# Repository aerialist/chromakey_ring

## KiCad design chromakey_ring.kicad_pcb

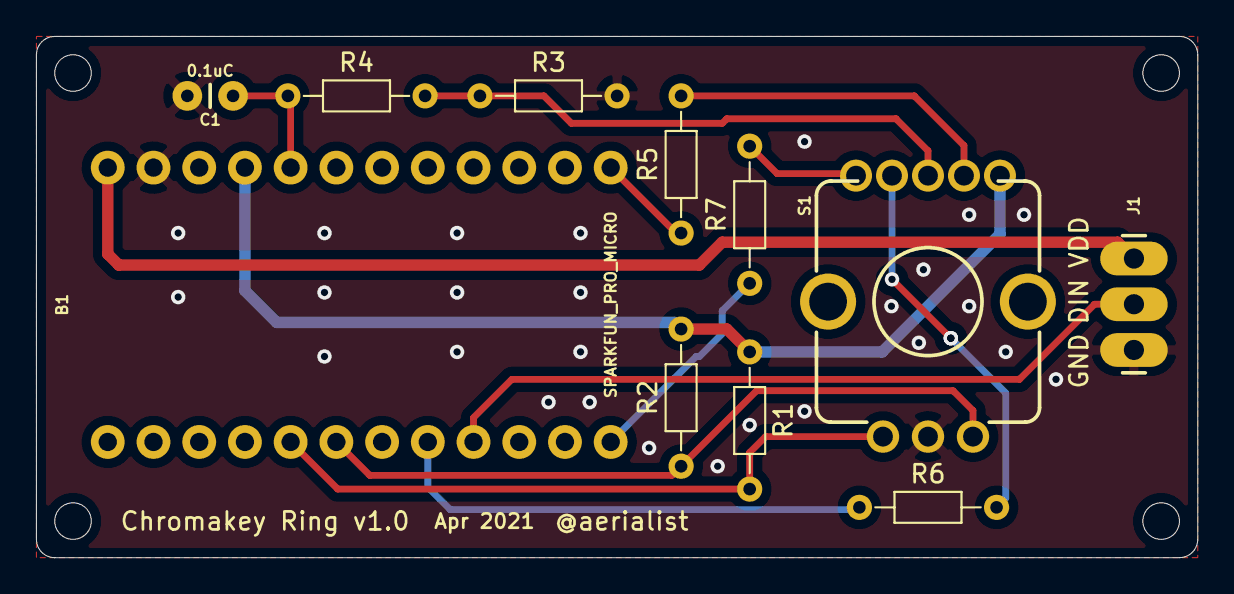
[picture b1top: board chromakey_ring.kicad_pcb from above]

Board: 2 copper layers, 64.5 x 29.0 mm, 11 parts (0 on the bottom side), 14 nets.

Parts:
B1: SPARKFUN_PRO_MICRO
C1: 0.1uC; CAP-PTH-2.54
J1: Conn_01x03; 1X03_LONGPADS
R1, R2, R3: 10kR; R_Axial_DIN0204_L3.6mm_D1.6mm_P7.62mm_Horizontal
R4: 1kR; R_Axial_DIN0204_L3.6mm_D1.6mm_P7.62mm_Horizontal
R5, R6, R7: 330R; R_Axial_DIN0204_L3.6mm_D1.6mm_P7.62mm_Horizontal
S1: ENCODER-RGB-SWITCH; ENCODER_LED_3

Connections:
+5V: B1.21, R1.1, R2.2, S1.5
/A: B1.5, R1.2, S1.A
/B: B1.6, R2.1, S1.B
/DIN: B1.9, J1.2
/LED_B: B1.13, R5.1
/LED_G: B1.8, R6.1
/LED_R: B1.12, R7.1
/SW: B1.20, C1.1, R4.1
GND: B1.23, C1.2, J1.3, R3.2, S1.C
unnamed: R3.1, R4.2, S1.3
unnamed: R5.2, S1.4
unnamed: R6.2, S1.2
unnamed: R7.2, S1.1
VD: B1.24, J1.1

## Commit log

2021-04-25 v1.0
2021-04-25 add schematics and layout pdf
2021-04-25 Add Arduino code
